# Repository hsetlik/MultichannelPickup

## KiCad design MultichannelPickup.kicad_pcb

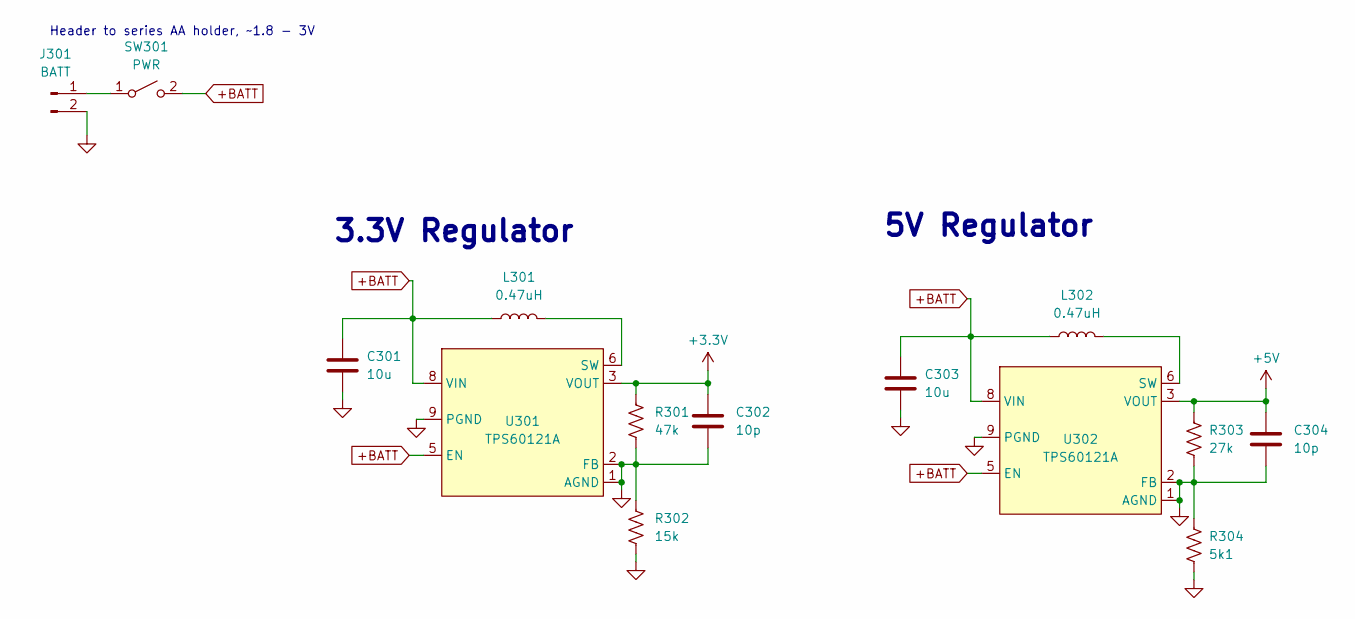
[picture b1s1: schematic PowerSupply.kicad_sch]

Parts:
C301, C303: 10u; C_0805_2012Metric
C302, C304: 10p; C_0805_2012Metric
J301: BATT; PinHeader_1x02_P2.54mm_Vertical
L301, L302: 0.47uH; L_Abracon_ASPI-4030S
R301: 47k; R_0805_2012Metric
R302: 15k; R_0805_2012Metric
R303: 27k; R_0805_2012Metric
R304: 5k1; R_0805_2012Metric
SW301: PWR; Switch_Toggle_SPST_SubMini
U301, U302: TPS60121A; WSON-8-1EP_2x2mm_P0.5mm_EP0.9x1.6mm

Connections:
+3.3V: C302.1, R301.1, U301.3 (VOUT), U301.4 (VOUT); also elsewhere on the board
+5V: C304.1, R303.1, U302.3 (VOUT), U302.4 (VOUT); also elsewhere on the board
+BATT: C301.1, C303.1, L301.1, L302.1, SW301.2 (B), U301.5 (EN), U301.8 (VIN), U302.5 (EN), U302.8 (VIN); also elsewhere on the board
GND: C301.2, C302.2, C303.2, C304.2, J301.2, R301.2, R302.1, R302.2, R303.2, R304.1, R304.2, U301.1 (AGND), U301.2 (FB), U301.9 (PGND), U302.1 (AGND), U302.2 (FB), U302.9 (PGND); also elsewhere on the board
unnamed: J301.1, SW301.1 (A)
unnamed: L301.2, U301.6 (SW), U301.7 (SW)
unnamed: L302.2, U302.6 (SW), U302.7 (SW)

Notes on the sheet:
5V Regulator
Header to series AA holder, ~1.8 - 3V
3.3V Regulator

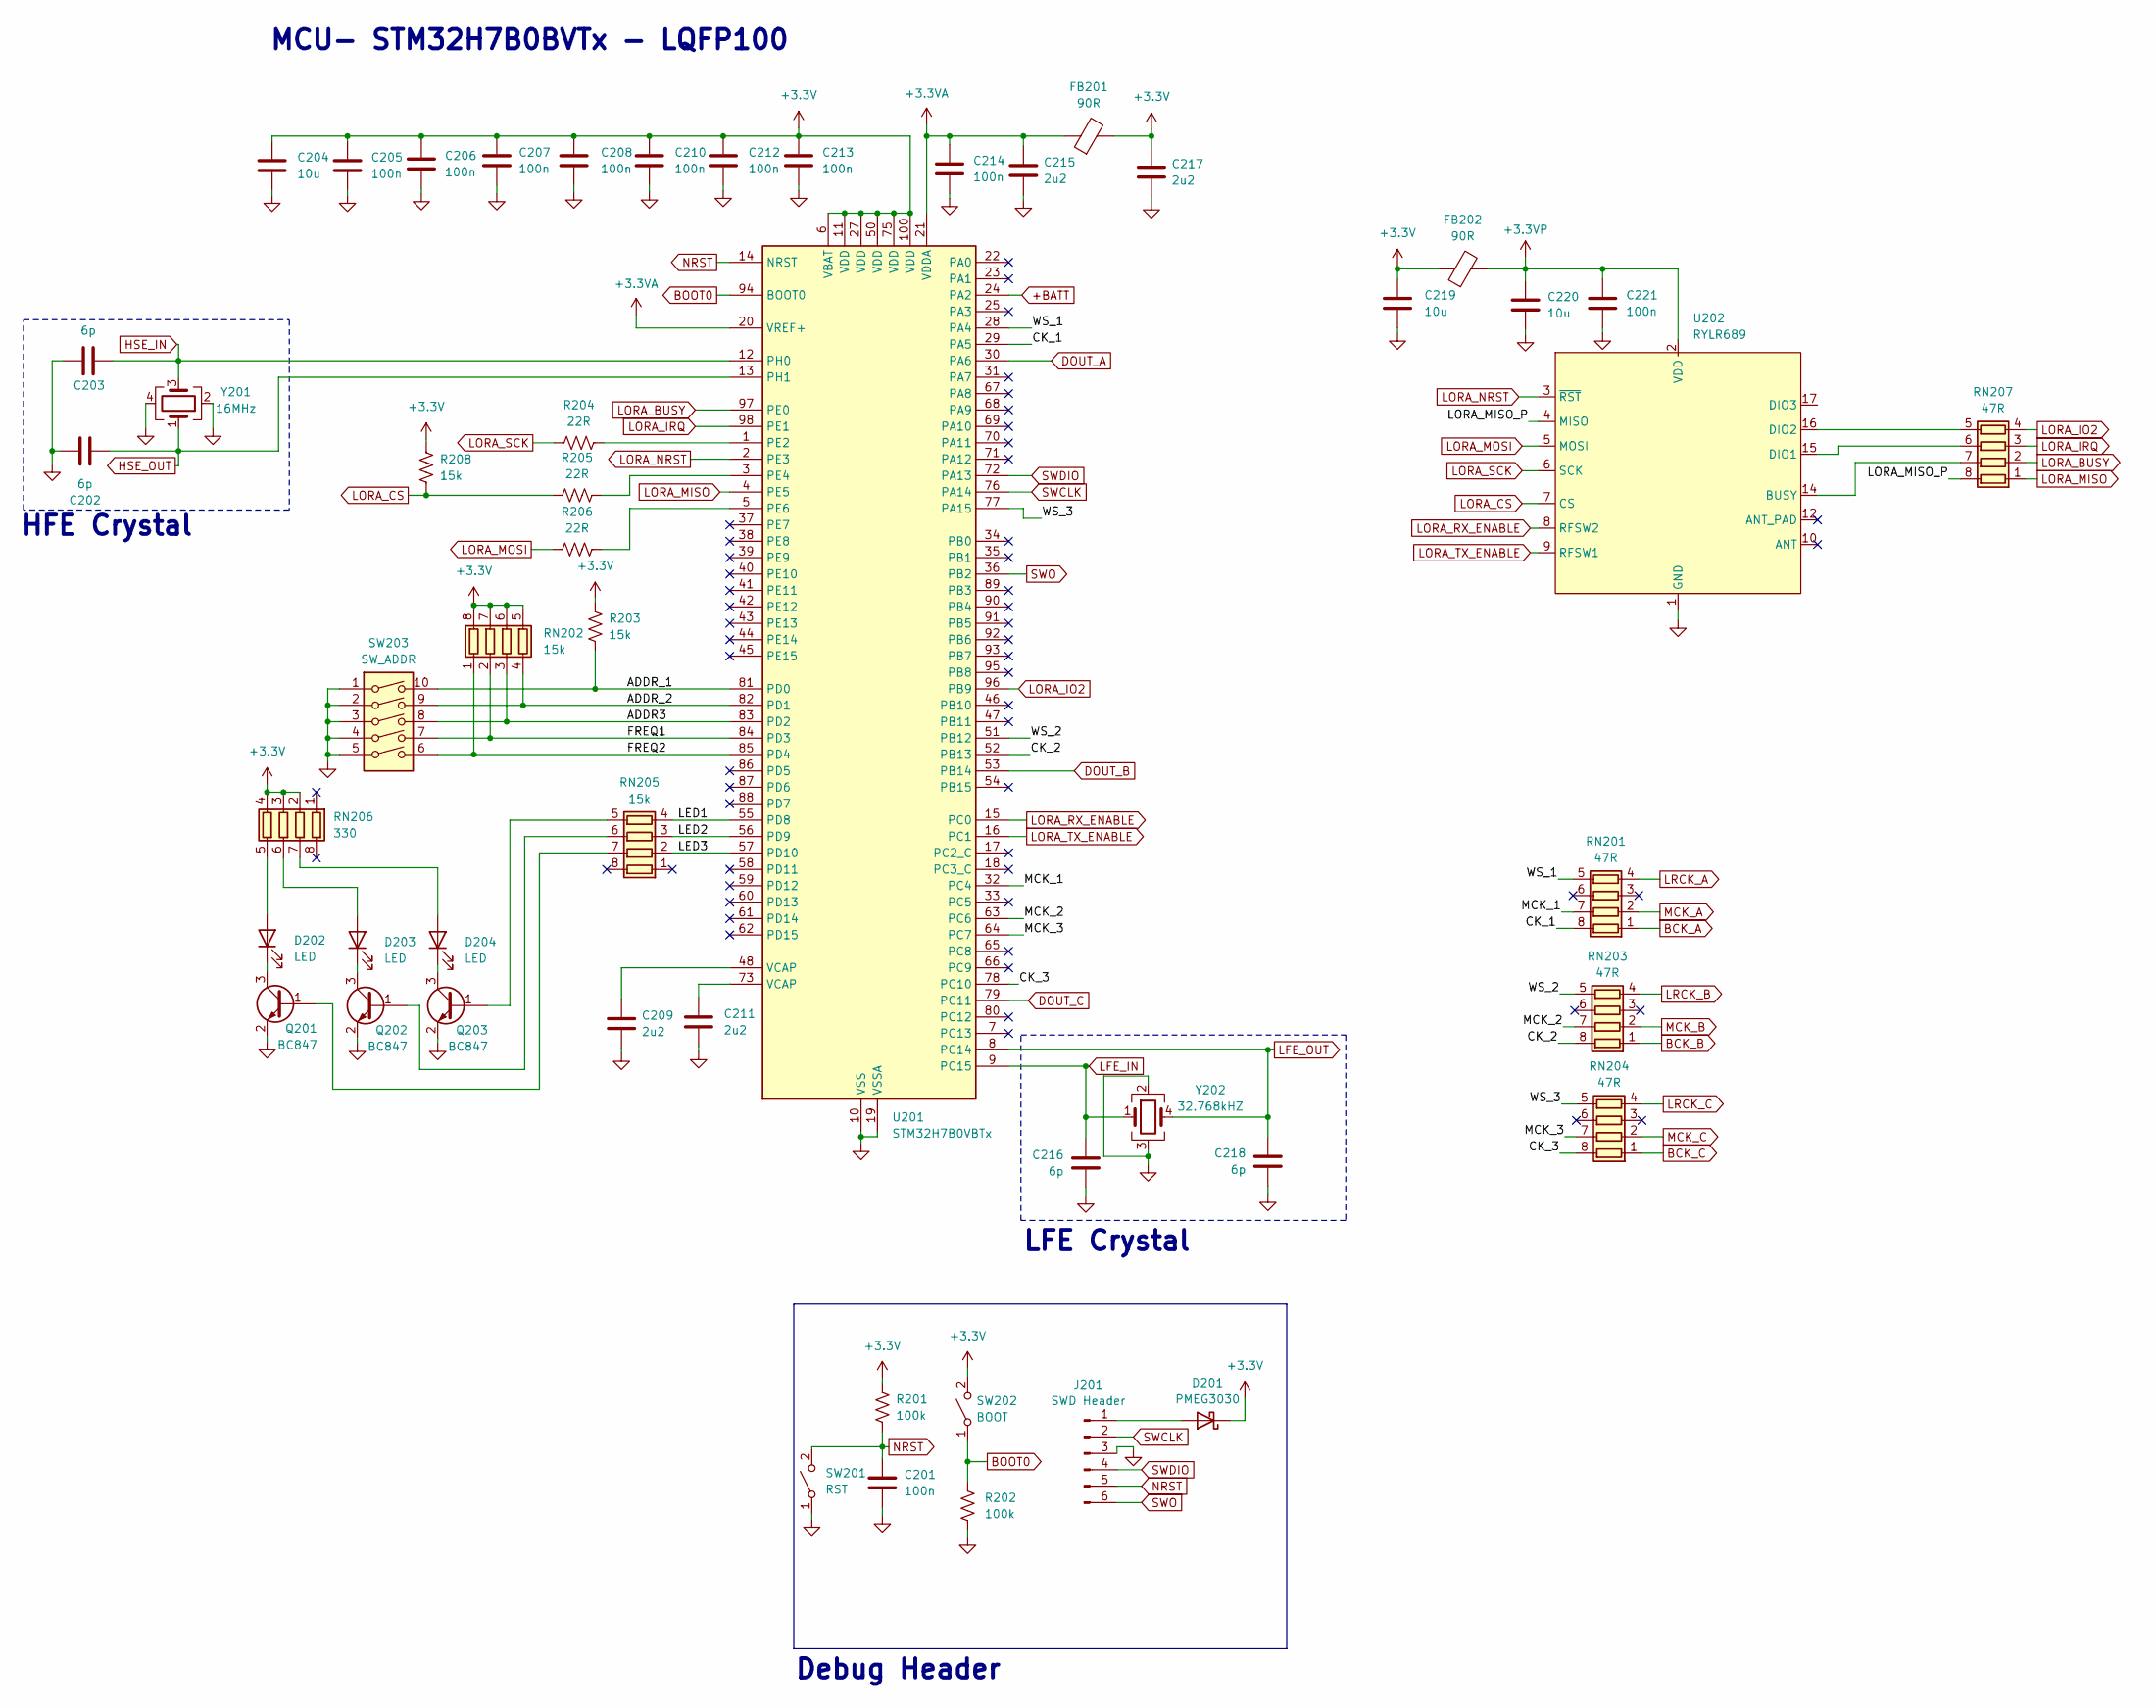
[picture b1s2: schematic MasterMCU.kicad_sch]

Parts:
C201, C205, C206, C207, C208, C210, C212, C213, C214, C221: 100n; C_0805_2012Metric
C202, C203, C216, C218: 6p; C_0805_2012Metric
C204, C219, C220: 10u; C_0805_2012Metric
C209, C211, C215, C217: 2u2; C_0805_2012Metric
D201: PMEG3030; D_SOD-123
D202, D203, D204: LED; LED_0805_2012Metric
FB201, FB202: 90R; R_0805_2012Metric
J201: SWD Header; PinHeader_1x06_P2.54mm_Vertical
Q201, Q202, Q203: BC847; SOT-23
R201, R202: 100k; R_0805_2012Metric
R203, R208: 15k; R_0805_2012Metric
R204, R205, R206: 22R; R_0805_2012Metric
RN201, RN203, RN204: 47R; R_Array_Concave_4x0603
RN202, RN205: 15k; R_Array_Concave_4x0603
RN206: 330; R_Array_Concave_4x0603
RN207: 47R; R_Array_Concave_4x0402
SW201: RST; SW_SPST_B3U-1000P
SW202: BOOT; SW_SPST_B3U-1000P
SW203: SW_ADDR; DIP-10_W7.62mm
U201: STM32H7B0VBTx; LQFP-100_14x14mm_P0.5mm
U202: RYLR689
Y201: 16MHz; Crystal_SMD_EuroQuartz_MT-4Pin_3.2x2.5mm
Y202: 32.768kHZ; Crystal_SMD_SeikoEpson_MC306-4Pin_8.0x3.2mm

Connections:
+3.3V: C204.1, C205.1, C206.1, C207.1, C208.1, C210.1, C212.1, C213.1, C217.1, C219.1, D201.1 (K), FB201.2, FB202.1, R201.1, R203.1, R208.1, RN202.5 (R4.2), RN202.6 (R3.2), RN202.7 (R2.2), RN202.8 (R1.2), RN206.2 (R2.1), RN206.3 (R3.1), RN206.4 (R4.1), SW202.2 (B), U201.6 (VBAT), U201.11 (VDD), U201.27 (VDD), U201.50 (VDD), U201.75 (VDD), U201.100 (VDD); also elsewhere on the board
+3.3VA: C214.1, C215.1, FB201.1, U201.20 (VREF+), U201.21 (VDDA)
+3.3VP: C220.1, C221.1, FB202.2, U202.2 (VDD)
+BATT: U201.24 (PA2); also elsewhere on the board
/MasterMCU/ADDR3: RN202.3 (R3.1), SW203.8, U201.83 (PD2)
/MasterMCU/ADDR_1: R203.2, SW203.10, U201.81 (PD0)
/MasterMCU/ADDR_2: RN202.4 (R4.1), SW203.9, U201.82 (PD1)
/MasterMCU/CK_1: RN201.8 (R1.2), U201.29 (PA5)
/MasterMCU/CK_2: RN203.8 (R1.2), U201.52 (PB13)
/MasterMCU/CK_3: RN204.8 (R1.2), U201.78 (PC10)
/MasterMCU/FREQ1: RN202.2 (R2.1), SW203.7, U201.84 (PD3)
/MasterMCU/FREQ2: RN202.1 (R1.1), SW203.6, U201.85 (PD4)
/MasterMCU/LED1: RN205.4 (R4.1), U201.55 (PD8)
/MasterMCU/LED2: RN205.3 (R3.1), U201.56 (PD9)
/MasterMCU/LED3: RN205.2 (R2.1), U201.57 (PD10)
/MasterMCU/LORA_MISO_P: RN207.8 (R1.2), U202.4 (MISO)
/MasterMCU/MCK_1: RN201.7 (R2.2), U201.32 (PC4)
/MasterMCU/MCK_2: RN203.7 (R2.2), U201.63 (PC6)
/MasterMCU/MCK_3: RN204.7 (R2.2), U201.64 (PC7)
/MasterMCU/WS_1: RN201.5 (R4.2), U201.28 (PA4)
/MasterMCU/WS_2: RN203.5 (R4.2), U201.51 (PB12)
/MasterMCU/WS_3: RN204.5 (R4.2), U201.77 (PA15)
BCK_A: RN201.1 (R1.1); also elsewhere on the board
BCK_B: RN203.1 (R1.1); also elsewhere on the board
BCK_C: RN204.1 (R1.1); also elsewhere on the board
BOOT0: R202.1, SW202.1 (A), U201.94 (BOOT0)
DOUT_A: U201.30 (PA6); also elsewhere on the board
DOUT_B: U201.53 (PB14); also elsewhere on the board
DOUT_C: U201.79 (PC11); also elsewhere on the board
GND: C201.2, C202.1, C203.1, C204.2, C205.2, C206.2, C207.2, C208.2, C209.2, C210.2, C211.2, C212.2, C213.2, C214.2, C215.2, C216.2, C217.2, C218.2, C219.2, C220.2, C221.2, J201.3, Q201.2 (E), Q202.2 (E), Q203.2 (E), R202.2, SW201.1 (A), SW203.1, SW203.2, SW203.3, SW203.4, SW203.5, U201.10 (VSS), U201.19 (VSSA), U201.26 (VSS), U201.49 (VSS), U201.74 (VSS), U201.99 (VSS), U202.1 (GND), U202.13 (GND), U202.18 (GND), Y201.2, Y201.4, Y202.2, Y202.3; also elsewhere on the board
HSE_IN: C203.2, U201.12 (PH0), Y201.3
HSE_OUT: C202.2, U201.13 (PH1), Y201.1
LFE_IN: C216.1, U201.9 (PC15), Y202.1
LFE_OUT: C218.1, U201.8 (PC14), Y202.4
LORA_BUSY: RN207.2 (R2.1), U201.97 (PE0)
LORA_CS: R205.1, R208.2, U202.7 (CS)
LORA_IO2: RN207.4 (R4.1), U201.96 (PB9)
LORA_IRQ: RN207.3 (R3.1), U201.98 (PE1)
LORA_MISO: RN207.1 (R1.1), U201.4 (PE5)
LORA_MOSI: R206.1, U202.5 (MOSI)
LORA_NRST: U201.2 (PE3), U202.3 (~RST)
LORA_RX_ENABLE: U201.15 (PC0), U202.8 (RFSW2)
LORA_SCK: R204.1, U202.6 (SCK)
LORA_TX_ENABLE: U201.16 (PC1), U202.9 (RFSW1)
LRCK_A: RN201.4 (R4.1); also elsewhere on the board
LRCK_B: RN203.4 (R4.1); also elsewhere on the board
LRCK_C: RN204.4 (R4.1); also elsewhere on the board
MCK_A: RN201.2 (R2.1); also elsewhere on the board
MCK_B: RN203.2 (R2.1); also elsewhere on the board
MCK_C: RN204.2 (R2.1); also elsewhere on the board
NRST: C201.1, J201.5, R201.2, SW201.2 (B), U201.14 (NRST)
unnamed: C209.1, U201.48 (VCAP)
unnamed: C211.1, U201.73 (VCAP)
unnamed: D201.2 (A), J201.1
unnamed: D202.2 (A), RN206.5 (R4.2)
unnamed: D202.1 (K), Q201.3 (C)
unnamed: D203.2 (A), RN206.6 (R3.2)
unnamed: D203.1 (K), Q202.3 (C)
unnamed: D204.2 (A), RN206.7 (R2.2)
unnamed: D204.1 (K), Q203.3 (C)
unnamed: Q201.1 (B), RN205.7 (R2.2)
unnamed: Q202.1 (B), RN205.6 (R3.2)
unnamed: Q203.1 (B), RN205.5 (R4.2)
unnamed: RN207.7 (R2.2), U202.14 (BUSY)
unnamed: RN207.6 (R3.2), U202.15 (DIO1)
unnamed: RN207.5 (R4.2), U202.16 (DIO2)
unnamed: R204.2, U201.1 (PE2)
unnamed: R205.2, U201.3 (PE4)
unnamed: R206.2, U201.5 (PE6)
SWCLK: J201.2, U201.76 (PA14)
SWDIO: J201.4, U201.72 (PA13)
SWO: J201.6, U201.36 (PB2)

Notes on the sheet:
MCU- STM32H7B0BVTx - LQFP100
LFE Crystal
Debug Header
HFE Crystal

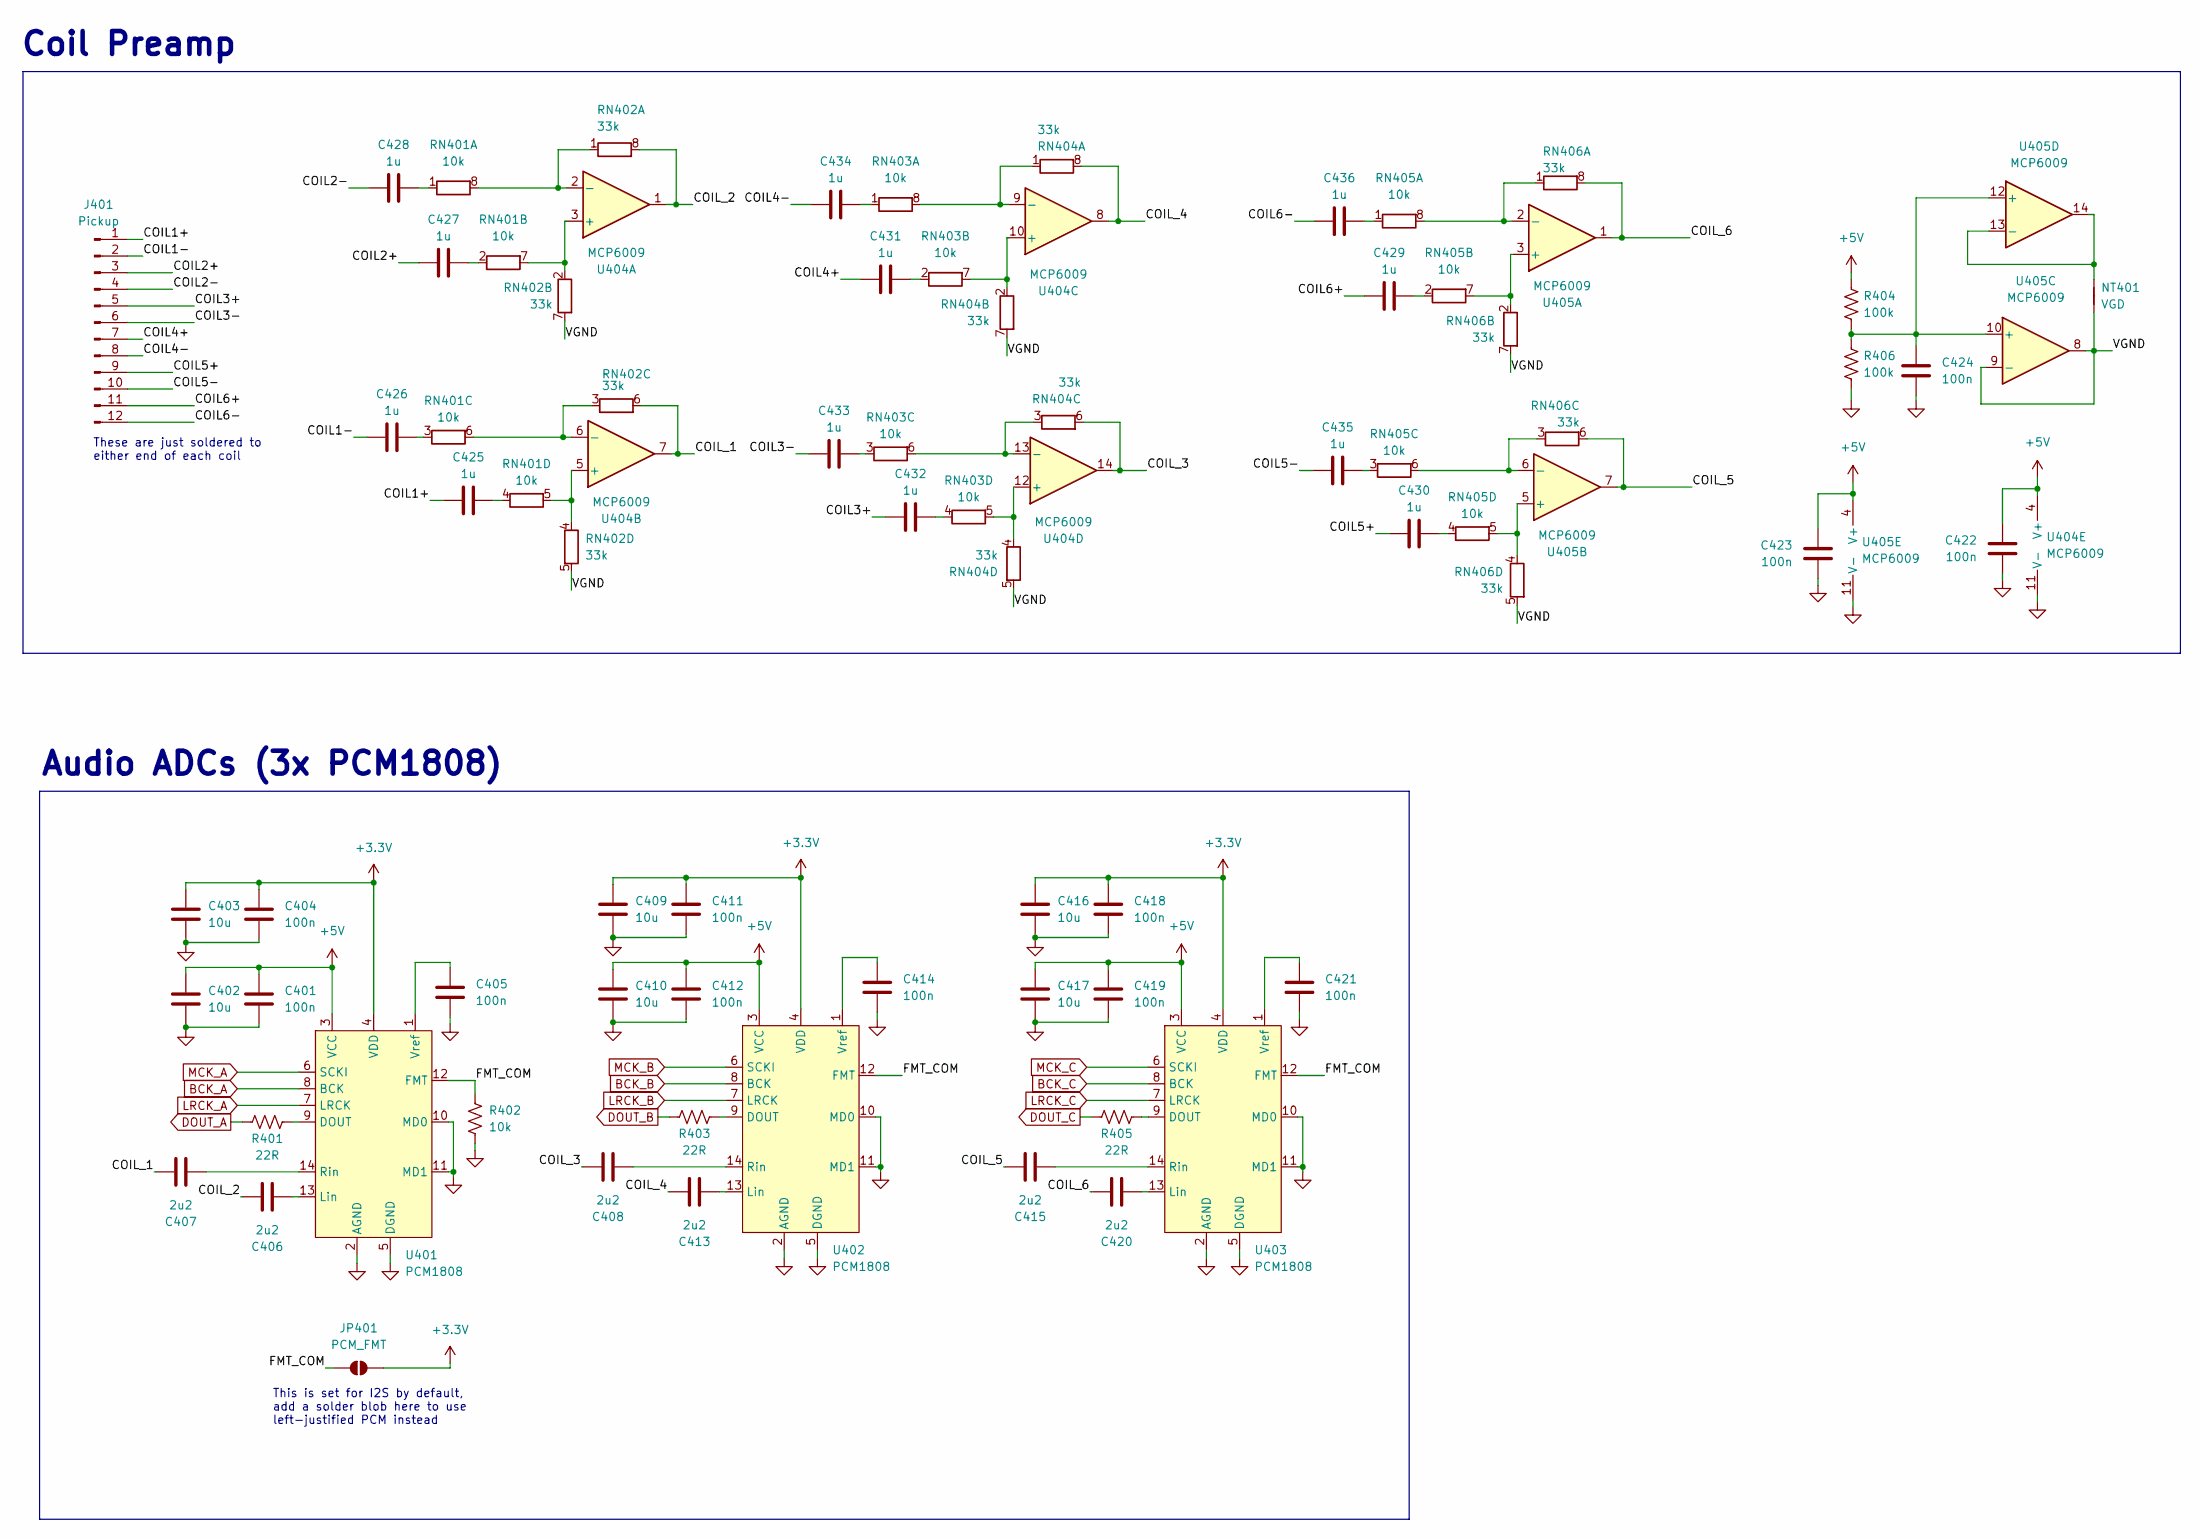
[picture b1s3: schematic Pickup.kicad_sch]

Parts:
C401, C404, C405, C411, C412, C414, C418, C419, C421, C422, C423, C424: 100n; C_0805_2012Metric
C402, C403, C409, C410, C416, C417: 10u; C_0805_2012Metric
C406, C407, C408, C413, C415, C420: 2u2; C_0805_2012Metric
C425, C426, C427, C428, C429, C430, C431, C432, C433, C434, C435, C436: 1u; C_0805_2012Metric
J401: Pickup; JST_PH_B12B-PH-K_1x12_P2.00mm_Vertical
JP401: PCM_FMT; SolderJumper-2_P1.3mm_Open_TrianglePad1.0x1.5mm
NT401: VGD; NetTie-2_SMD_Pad0.5mm
R401, R403, R405: 22R; R_0805_2012Metric
R402: 10k; R_0805_2012Metric
R404, R406: 100k; R_0805_2012Metric
RN401, RN403, RN405: 10k; R_Array_Concave_4x0603
RN402, RN404, RN406: 33k; R_Array_Concave_4x0603
U401, U402, U403: PCM1808; TSSOP-14_4.4x5mm_P0.65mm
U404, U405: MCP6009; TSSOP-14_4.4x5mm_P0.65mm

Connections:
+3.3V: C403.1, C404.1, C409.1, C411.1, C416.1, C418.1, JP401.2 (B), U401.4 (VDD), U402.4 (VDD), U403.4 (VDD); also elsewhere on the board
+5V: C401.1, C402.1, C410.1, C412.1, C417.1, C419.1, C422.1, C423.1, R404.1, U401.3 (VCC), U402.3 (VCC), U403.3 (VCC), U404.4 (V+), U405.4 (V+); also elsewhere on the board
/Pickup/COIL1+: C425.1, J401.1
/Pickup/COIL1-: C426.1, J401.2
/Pickup/COIL2+: C427.1, J401.3
/Pickup/COIL2-: C428.1, J401.4
/Pickup/COIL3+: C432.1, J401.5
/Pickup/COIL3-: C433.1, J401.6
/Pickup/COIL4+: C431.1, J401.7
/Pickup/COIL4-: C434.1, J401.8
/Pickup/COIL5+: C430.1, J401.9
/Pickup/COIL5-: C435.1, J401.10
/Pickup/COIL6+: C429.1, J401.11
/Pickup/COIL6-: C436.1, J401.12
/Pickup/COIL_1: C407.2, RN402.6 (R3.2), U404.7
/Pickup/COIL_2: C406.2, RN402.8 (R1.2), U404.1
/Pickup/COIL_3: C408.2, RN404.6 (R3.2), U404.14
/Pickup/COIL_4: C413.2, RN404.8 (R1.2), U404.8
/Pickup/COIL_5: C415.2, RN406.6 (R3.2), U405.7
/Pickup/COIL_6: C420.2, RN406.8 (R1.2), U405.1
/Pickup/FMT_COM: JP401.1 (A), R402.1, U401.12 (FMT), U402.12 (FMT), U403.12 (FMT)
/Pickup/VGND: NT401.1, RN402.5 (R4.2), RN402.7 (R2.2), RN404.5 (R4.2), RN404.7 (R2.2), RN406.5 (R4.2), RN406.7 (R2.2), U405.8, U405.9 (-)
BCK_A: U401.8 (BCK); also elsewhere on the board
BCK_B: U402.8 (BCK); also elsewhere on the board
BCK_C: U403.8 (BCK); also elsewhere on the board
DOUT_A: R401.1; also elsewhere on the board
DOUT_B: R403.1; also elsewhere on the board
DOUT_C: R405.1; also elsewhere on the board
GND: C401.2, C402.2, C403.2, C404.2, C405.2, C409.2, C410.2, C411.2, C412.2, C414.2, C416.2, C417.2, C418.2, C419.2, C421.2, C422.2, C423.2, C424.2, R402.2, R406.2, U401.2 (AGND), U401.5 (DGND), U401.10 (MD0), U401.11 (MD1), U402.2 (AGND), U402.5 (DGND), U402.10 (MD0), U402.11 (MD1), U403.2 (AGND), U403.5 (DGND), U403.10 (MD0), U403.11 (MD1), U404.11 (V-), U405.11 (V-); also elsewhere on the board
LRCK_A: U401.7 (LRCK); also elsewhere on the board
LRCK_B: U402.7 (LRCK); also elsewhere on the board
LRCK_C: U403.7 (LRCK); also elsewhere on the board
MCK_A: U401.6 (SCKI); also elsewhere on the board
MCK_B: U402.6 (SCKI); also elsewhere on the board
MCK_C: U403.6 (SCKI); also elsewhere on the board
unnamed: C428.2, RN401.1 (R1.1)
unnamed: RN401.8 (R1.2), RN402.1 (R1.1), U404.2 (-)
unnamed: C427.2, RN401.2 (R2.1)
unnamed: RN401.7 (R2.2), RN402.2 (R2.1), U404.3 (+)
unnamed: C426.2, RN401.3 (R3.1)
unnamed: RN401.6 (R3.2), RN402.3 (R3.1), U404.6 (-)
unnamed: C425.2, RN401.4 (R4.1)
unnamed: RN401.5 (R4.2), RN402.4 (R4.1), U404.5 (+)
unnamed: C434.2, RN403.1 (R1.1)
unnamed: RN403.8 (R1.2), RN404.1 (R1.1), U404.9 (-)
unnamed: C431.2, RN403.2 (R2.1)
unnamed: RN403.7 (R2.2), RN404.2 (R2.1), U404.10 (+)
unnamed: C433.2, RN403.3 (R3.1)
unnamed: RN403.6 (R3.2), RN404.3 (R3.1), U404.13 (-)
unnamed: C432.2, RN403.4 (R4.1)
unnamed: RN403.5 (R4.2), RN404.4 (R4.1), U404.12 (+)
unnamed: C436.2, RN405.1 (R1.1)
unnamed: RN405.8 (R1.2), RN406.1 (R1.1), U405.2 (-)
unnamed: C429.2, RN405.2 (R2.1)
unnamed: RN405.7 (R2.2), RN406.2 (R2.1), U405.3 (+)
unnamed: C435.2, RN405.3 (R3.1)
unnamed: RN405.6 (R3.2), RN406.3 (R3.1), U405.6 (-)
unnamed: C430.2, RN405.4 (R4.1)
unnamed: RN405.5 (R4.2), RN406.4 (R4.1), U405.5 (+)
unnamed: R401.2, U401.9 (DOUT)
unnamed: C406.1, U401.13 (Lin)
unnamed: C407.1, U401.14 (Rin)
unnamed: C405.1, U401.1 (Vref)
unnamed: R403.2, U402.9 (DOUT)
unnamed: C413.1, U402.13 (Lin)
unnamed: C408.1, U402.14 (Rin)
unnamed: C414.1, U402.1 (Vref)
unnamed: R405.2, U403.9 (DOUT)
unnamed: C420.1, U403.13 (Lin)
unnamed: C415.1, U403.14 (Rin)
unnamed: C421.1, U403.1 (Vref)
unnamed: C424.1, R404.2, R406.1, U405.10 (+), U405.12 (+)
unnamed: NT401.2, U405.13 (-), U405.14

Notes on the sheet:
Coil Preamp
These are just soldered to either end of each coil
Audio ADCs (3x PCM1808)
This is set for I2S by default, add a solder blob here to use left-justified PCM instead

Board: 4 copper layers, 122 parts (2 on the bottom side), 134 nets, no tracks yet.

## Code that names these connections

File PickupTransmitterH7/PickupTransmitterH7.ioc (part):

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Mcu.Name=STM32H7B0VBTx
Mcu.Package=LQFP100
Mcu.UserName=STM32H7B0VBTx
PA13.Mode=Trace_Asynchronous_SW
PA13.Signal=DEBUG_JTMS-SWDIO
PA14.Mode=Trace_Asynchronous_SW
PA14.Signal=DEBUG_JTCK-SWCLK
PA15.Mode=Half_Duplex_Master_Rx
PA15.Signal=I2S3_WS
PA2.GPIOParameters=GPIO_Label
PA2.GPIO_Label=BATT
PA2.Signal=ADCx_INP14
PA4.Mode=Half_Duplex_Master_Rx
PA4.Signal=I2S1_WS
PA5.Mode=Half_Duplex_Master_Rx
PA5.Signal=I2S1_CK
PA6.Mode=Half_Duplex_Master_Rx
PA6.Signal=I2S1_SDI
PB12.Mode=Half_Duplex_Master_Rx
PB12.Signal=I2S2_WS
PB13.Mode=Half_Duplex_Master_Rx
PB13.Signal=I2S2_CK
PB14.Mode=Half_Duplex_Master_Rx
PB14.Signal=I2S2_SDI
PB3.Mode=Trace_Asynchronous_SW
PB3.Signal=DEBUG_JTDO-SWO
PB9.GPIOParameters=GPIO_Label
PB9.GPIO_Label=LORA_IO2
PB9.Signal=GPIO_Input
PC0.GPIOParameters=GPIO_Label
PC0.GPIO_Label=LORA_RX_ENABLE
PC0.Signal=GPIO_Output
PC1.GPIOParameters=GPIO_Label
PC1.GPIO_Label=LORA_TX_ENABLE
PC1.Signal=GPIO_Output
PC10.Mode=Half_Duplex_Master_Rx
PC10.Signal=I2S3_CK
PC11.Mode=Half_Duplex_Master_Rx
PC11.Signal=I2S3_SDI
PC14-OSC32_IN.Mode=LSE-External-Oscillator
PC14-OSC32_IN.Signal=RCC_OSC32_IN
PC15-OSC32_OUT.Mode=LSE-External-Oscillator
PC15-OSC32_OUT.Signal=RCC_OSC32_OUT
PC4.Mode=Master_Clock_Activated
PC4.Signal=I2S1_MCK
PC6.Mode=Master_Clock_Activated
PC6.Signal=I2S2_MCK
PC7.Mode=Master_Clock_Activated
PC7.Signal=I2S3_MCK
PD0.GPIOParameters=GPIO_Label
PD0.GPIO_Label=ADR1
PD0.Signal=GPIO_Input
PD1.GPIOParameters=GPIO_Label
PD1.GPIO_Label=ADR2
PD1.Signal=GPIO_Input
PD10.GPIOParameters=GPIO_Label
PD10.GPIO_Label=LED3
PD10.Signal=GPIO_Output
PD2.GPIOParameters=GPIO_Label
PD2.GPIO_Label=ADR3
PD2.Signal=GPIO_Input
PD3.GPIOParameters=GPIO_Label
PD3.GPIO_Label=FREQ1
PD3.Signal=GPIO_Input
PD4.GPIOParameters=GPIO_Label
PD4.GPIO_Label=FREQ2
PD4.Signal=GPIO_Input
PD8.GPIOParameters=GPIO_Label
PD8.GPIO_Label=LED1
PD8.Signal=GPIO_Output
PD9.GPIOParameters=GPIO_Label
PD9.GPIO_Label=LED2
PD9.Signal=GPIO_Output
PE0.GPIOParameters=GPIO_Label
PE0.GPIO_Label=LORA_BUSY
PE0.Signal=GPIO_Input
PE1.GPIOParameters=GPIO_Label
PE1.GPIO_Label=LORA_IRQ
PE1.Signal=GPXTI1
PE2.GPIOParameters=GPIO_Label
PE2.GPIO_Label=LORA_SCK
PE2.Mode=Full_Duplex_Master
PE2.Signal=SPI4_SCK
PE3.GPIOParameters=GPIO_Label
PE3.GPIO_Label=LORA_NRST
PE3.Signal=GPIO_Output
PE4.GPIOParameters=GPIO_Label
PE4.GPIO_Label=LORA_CS
PE4.Mode=NSS_Signal_Hard_Output
PE4.Signal=SPI4_NSS
PE5.GPIOParameters=GPIO_Label
PE5.GPIO_Label=LORA_MISO
PE5.Mode=Full_Duplex_Master
PE5.Signal=SPI4_MISO
PE6.GPIOParameters=GPIO_Label
PE6.GPIO_Label=LORA_MOSI
PE6.Mode=Full_Duplex_Master
PE6.Signal=SPI4_MOSI
PH0-OSC_IN.Mode=HSE-External-Oscillator
PH0-OSC_IN.Signal=RCC_OSC_IN
PH1-OSC_OUT.Mode=HSE-External-Oscillator
PH1-OSC_OUT.Signal=RCC_OSC_OUT
RCC.HSE_VALUE=32000000
RCC.SYSCLKFreq_VALUE=64000000
RCC.SYSCLKSource=RCC_SYSCLKSOURCE_PLLCLK
board=custom

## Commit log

2024-10-18 added code boilerplate
2024-10-23 PSU and audio ADC schematic
2024-10-24 new h7 boilerplate
2024-10-25 tracked drivers
2024-10-25 DMA & double buffering set up
2024-10-25 added float parsing and 6-string ring buffer
2024-10-25 installed Semtech LLCC68 RF driver
2024-10-29 STM32 pinout
2024-10-29 peripheral schematic stuff
2024-10-29 SWD header
2024-10-30 LEDs and footprints
2024-10-30 board start
2024-10-30 RF schematic drawn
2024-10-30 op amp input stage
2024-10-30 resistor array routing fix
